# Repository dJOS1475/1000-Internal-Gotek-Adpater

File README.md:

# 1000-Internal-Gotek-Adpater
Tandy 1000 Internal Gotek Adpater

This Tandy 1000 Internal Gotek Adapter allows you to use Gotek Virtual Floppy Drives with Tandy 1000's that send power over the Floppy cable.

Tandy 1000's that have power supplied via the Floppy Cable include the SL/2, TX, TL, TL/2, TL/3.

I made these because many folks wanted to use Gotek Virtual Floppy Drives with their Tandy's but due to the non-standard power-over-cable-design were unable to.

I highly recommend using the free FlashFloppy Firmware on Gotek Drives as the stock FW is quite poor. On my TL/2, I found that the FlashFloppy FF.CFG file needs the "pin34" option set to "chg" to enable Disk Change detection.

My Store can be found here: https://www.tindie.com/stores/CyberneticSys/

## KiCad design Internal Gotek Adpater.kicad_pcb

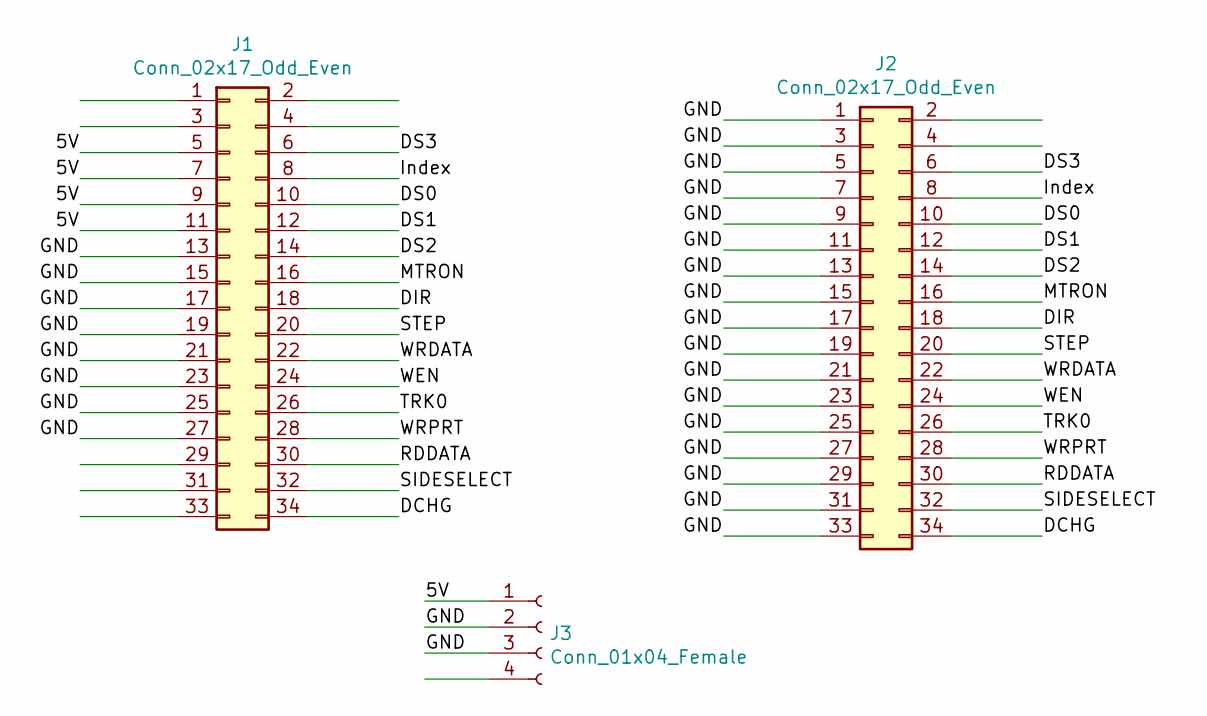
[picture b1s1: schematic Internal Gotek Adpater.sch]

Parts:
J1: Conn_02x17_Odd_Even; IDC34M
J2: Conn_02x17_Odd_Even; IDC34F
J3: Conn_01x04_Female; PinSocket_1x04_P2.54mm_Vertical

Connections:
/5V: J1.5, J1.7, J1.9, J1.11, J3.1
/DCHG: J1.34, J2.34
/DIR: J1.18, J2.18
/DS0: J1.10, J2.10
/DS1: J1.12, J2.12
/DS2: J1.14, J2.14
/DS3: J1.6, J2.6
/GND: J1.13, J1.15, J1.17, J1.19, J1.21, J1.23, J1.25, J1.27, J2.1, J2.3, J2.5, J2.7, J2.9, J2.11, J2.13, J2.15, J2.17, J2.19, J2.21, J2.23, J2.25, J2.27, J2.29, J2.31, J2.33, J3.2, J3.3
/Index: J1.8, J2.8
/MTRON: J1.16, J2.16
/RDDATA: J1.30, J2.30
/SIDESELECT: J1.32, J2.32
/STEP: J1.20, J2.20
/TRK0: J1.26, J2.26
/WEN: J1.24, J2.24
/WRDATA: J1.22, J2.22
/WRPRT: J1.28, J2.28

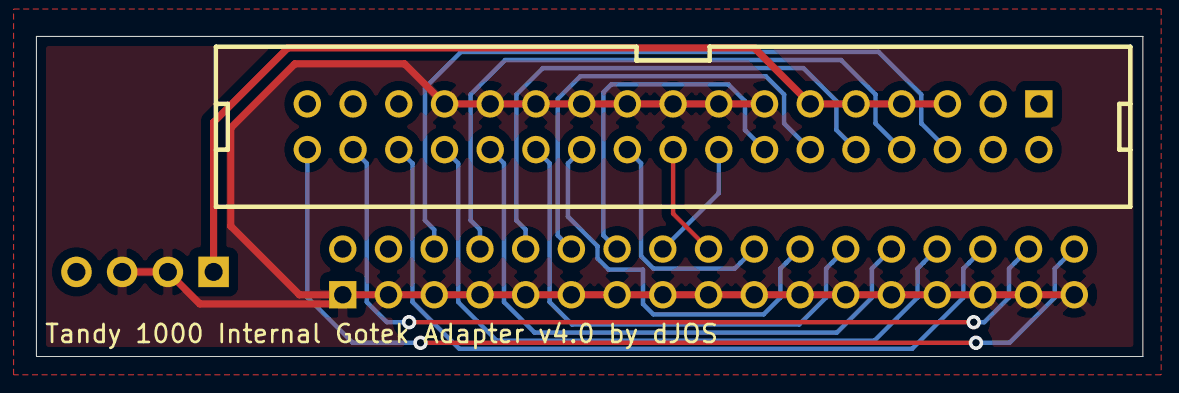
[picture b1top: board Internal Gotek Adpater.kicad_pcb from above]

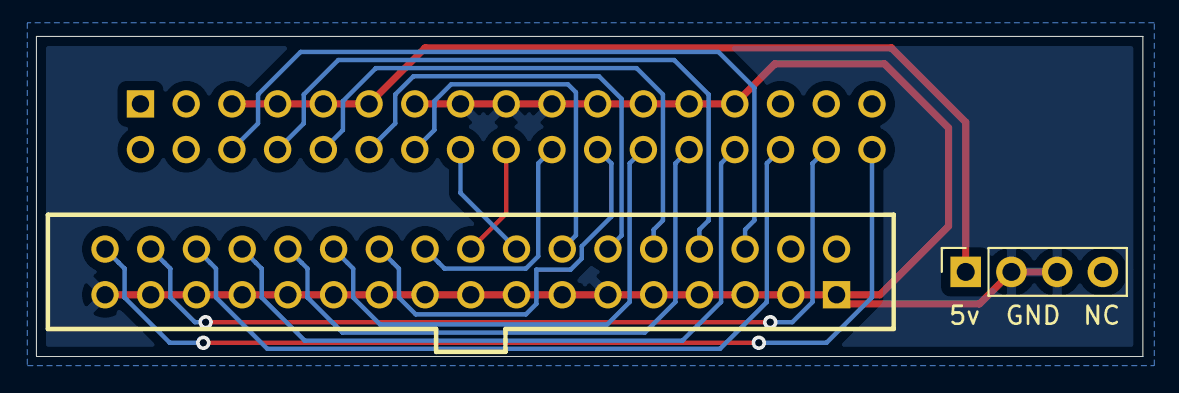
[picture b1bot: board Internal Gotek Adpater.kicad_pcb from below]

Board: 2 copper layers, 61.5 x 17.8 mm, 3 parts (2 on the bottom side), 17 nets.
